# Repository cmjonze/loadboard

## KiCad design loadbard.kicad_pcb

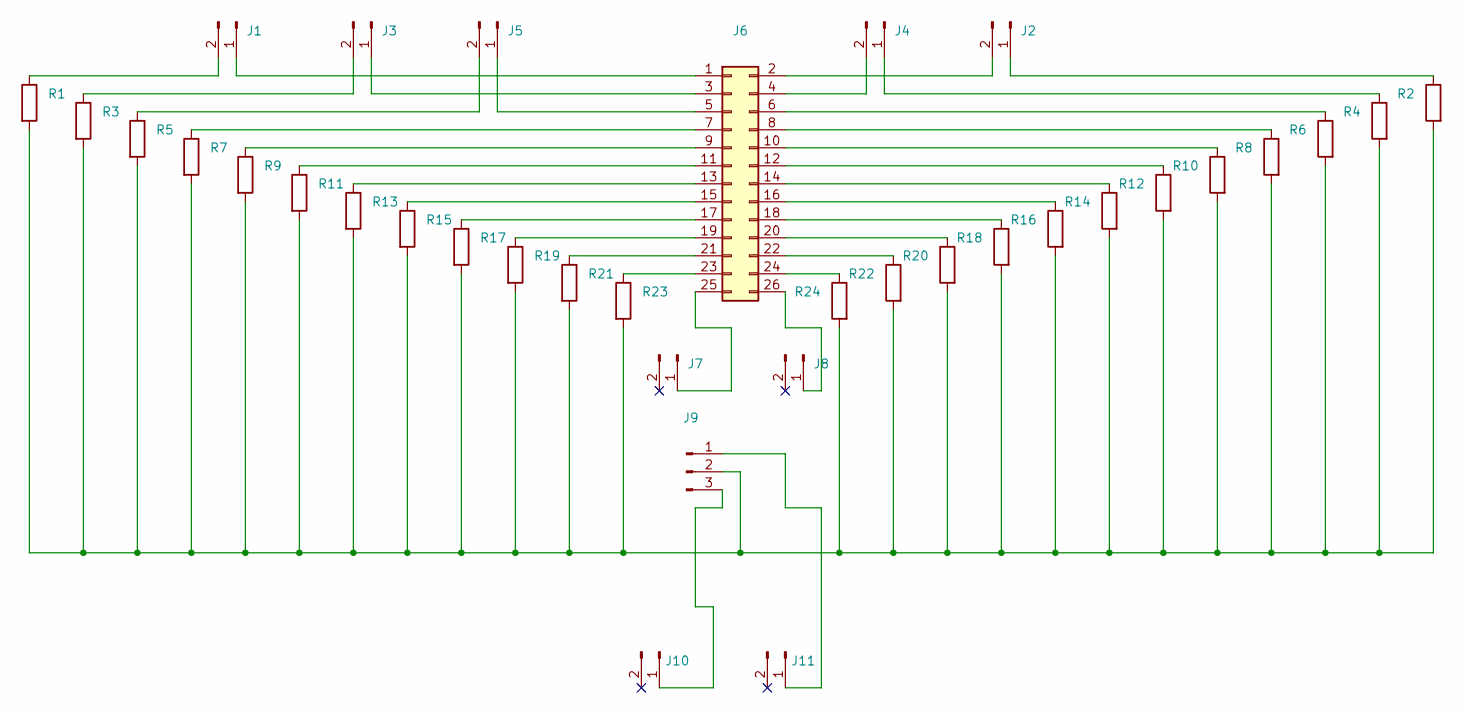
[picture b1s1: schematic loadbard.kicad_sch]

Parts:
J1, J2, J3, J4, J5, J7, J8, J10, J11: PinHeader_1x02_P2.54mm_Vertical
J6: PinSocket_2x13_P2.54mm_Vertical
J9: PinHeader_1x03_P2.54mm_Vertical
R1, R2, R3, R4, R5, R6, R7, R8, R9, R10, R11, R12, R13, R14, R15, R16, R17, R18, R19, R20, R21, R22, R23, R24: R_Axial_DIN0207_L6.3mm_D2.5mm_P10.16mm_Horizontal

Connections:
unnamed: J1.1, J6.1
unnamed: J1.2, R1.1
unnamed: J2.1, R2.1
unnamed: J2.2, J6.2
unnamed: J3.1, J6.3
unnamed: J3.2, R3.1
unnamed: J4.1, R4.1
unnamed: J4.2, J6.4
unnamed: J5.1, J6.5
unnamed: J5.2, R5.1
unnamed: J6.6, R6.1
unnamed: J6.7, R7.1
unnamed: J6.8, R8.1
unnamed: J6.9, R9.1
unnamed: J6.10, R10.1
unnamed: J6.11, R11.1
unnamed: J6.12, R12.1
unnamed: J6.13, R13.1
unnamed: J6.14, R14.1
unnamed: J6.15, R15.1
unnamed: J6.16, R16.1
unnamed: J6.17, R17.1
unnamed: J6.18, R18.1
unnamed: J6.19, R19.1
unnamed: J6.20, R20.1
unnamed: J6.21, R21.1
unnamed: J6.22, R22.1
unnamed: J6.23, R23.1
unnamed: J6.24, R24.1
unnamed: J6.25, J7.1
unnamed: J6.26, J8.1
unnamed: J9.2, R1.2, R2.2, R3.2, R4.2, R5.2, R6.2, R7.2, R8.2, R9.2, R10.2, R11.2, R12.2, R13.2, R14.2, R15.2, R16.2, R17.2, R18.2, R19.2, R20.2, R21.2, R22.2, R23.2, R24.2
unnamed: J9.3, J10.1
unnamed: J9.1, J11.1

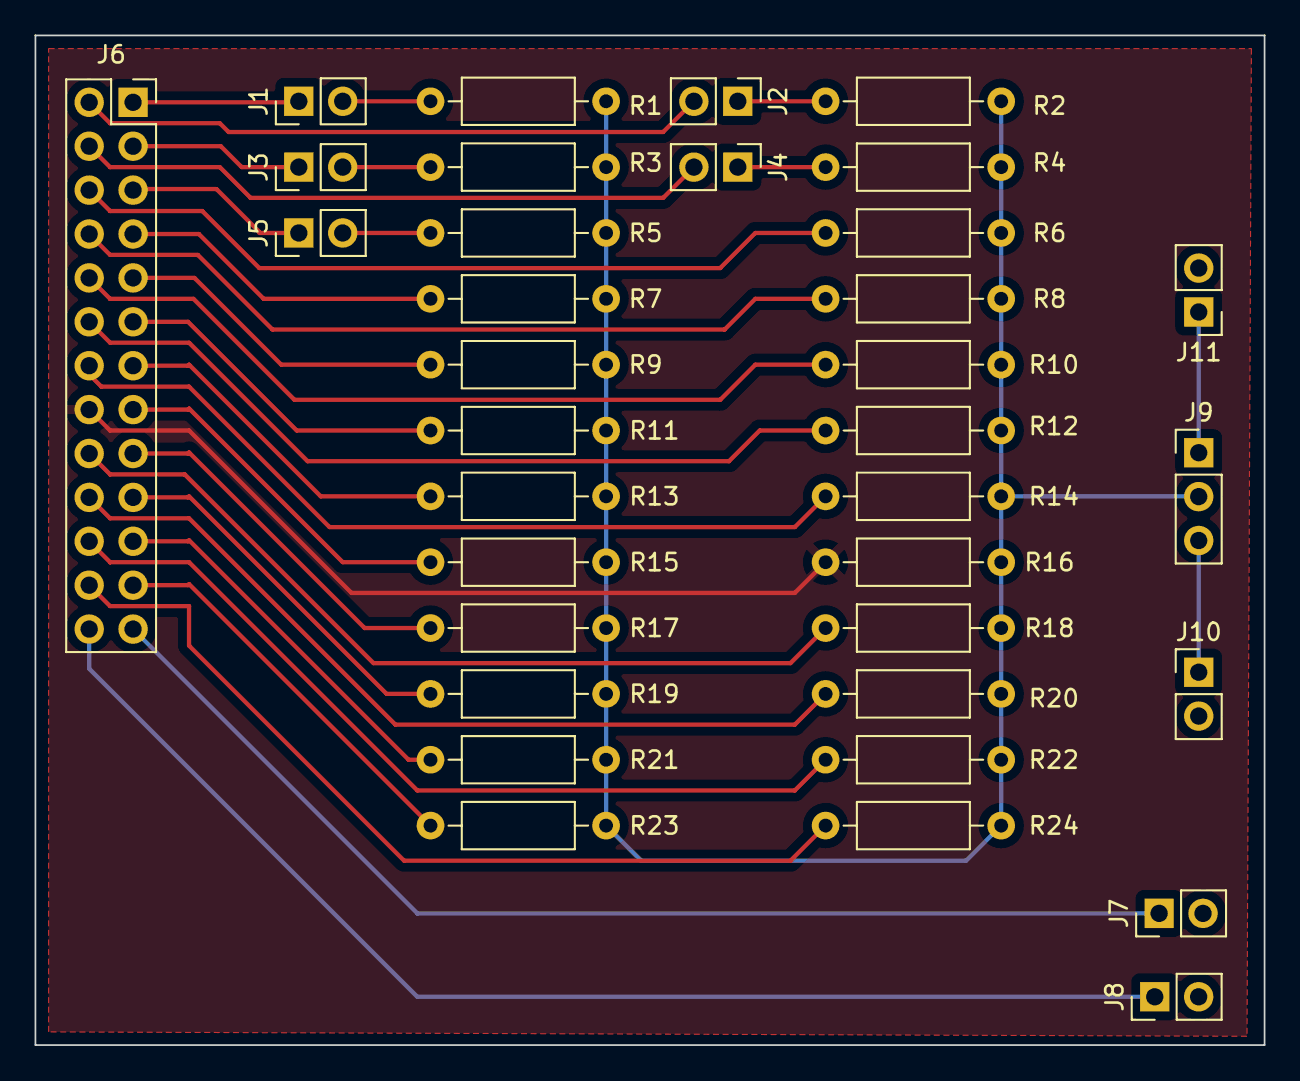
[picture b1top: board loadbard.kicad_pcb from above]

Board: 2 copper layers, 71.1 x 58.4 mm, 35 parts (0 on the bottom side), 34 nets.

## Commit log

2022-11-02 working
